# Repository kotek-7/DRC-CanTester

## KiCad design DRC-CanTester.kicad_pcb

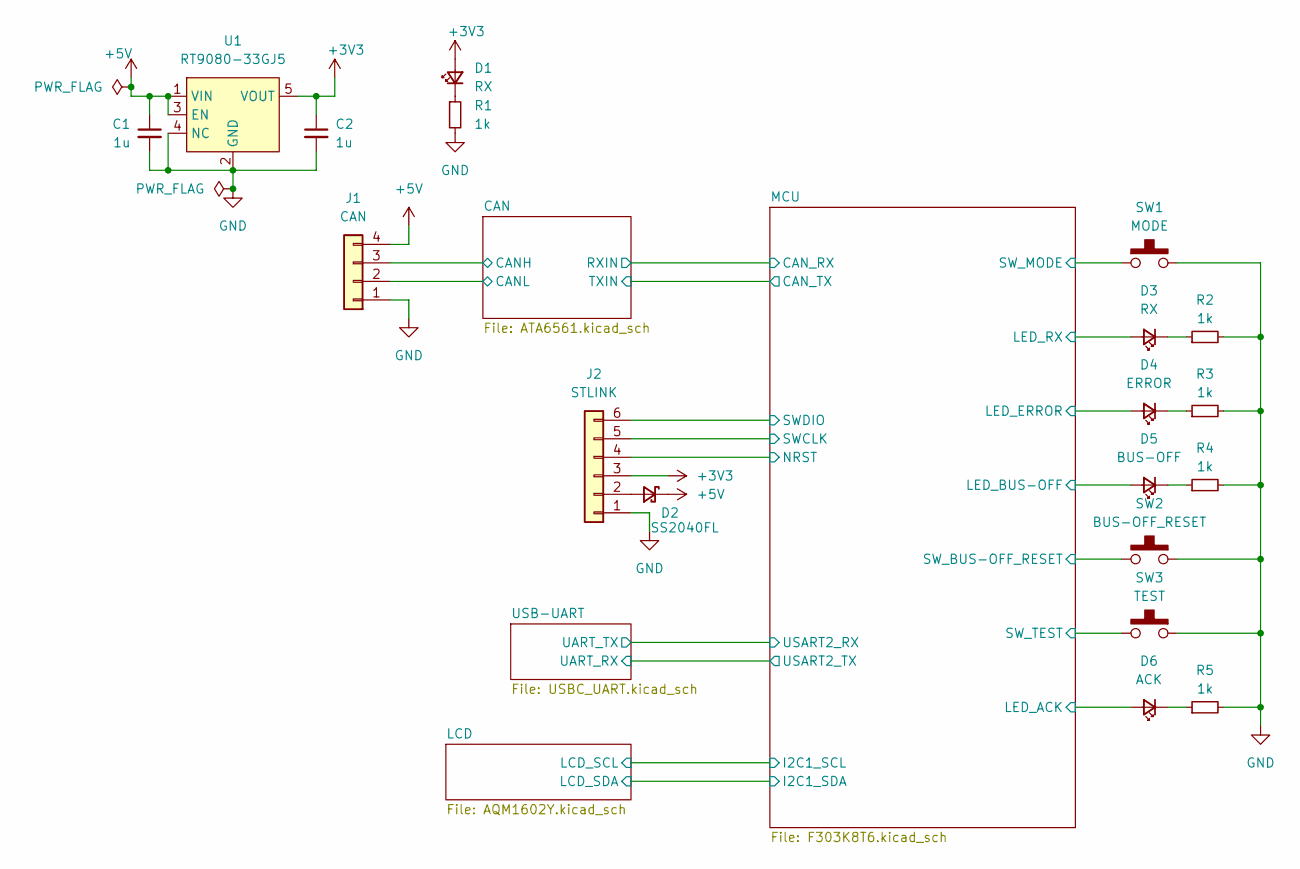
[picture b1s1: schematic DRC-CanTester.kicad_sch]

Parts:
C1, C2: 1u; C_0805_2012Metric_Pad1.18x1.45mm_HandSolder
D1, D3: RX; LED_0603_1608Metric_Pad1.05x0.95mm_HandSolder
D2: SS2040FL; D_SOD-123F
D4: ERROR; LED_0603_1608Metric_Pad1.05x0.95mm_HandSolder
D5: BUS-OFF; LED_0603_1608Metric_Pad1.05x0.95mm_HandSolder
D6: ACK; LED_0603_1608Metric_Pad1.05x0.95mm_HandSolder
J1: CAN; JST_XH_S4B-XH-A_1x04_P2.50mm_Horizontal; LCSC x
J2: STLINK; IDC-Header_2x03_P2.54mm_Vertical
R1, R2, R3, R4, R5: 1k; R_0603_1608Metric_Pad0.98x0.95mm_HandSolder
SW1: MODE; TS-06104
SW2: BUS-OFF_RESET; TS-06104
SW3: TEST; TS-06104
U1: RT9080-33GJ5; TSOT-23-5

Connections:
+3V3: C2.1, D1.2 (A), J2.3, U1.5 (VOUT); also elsewhere on the board
+5V: C1.1, D2.1 (K), J1.4, U1.1 (VIN), U1.3 (EN); also elsewhere on the board
/CAN/CANH: J1.3; also elsewhere on the board
/CAN/CANL: J1.2; also elsewhere on the board
/MCU/LED_ACK: D6.2 (A); also elsewhere on the board
/MCU/LED_BUS-OFF: D5.2 (A); also elsewhere on the board
/MCU/LED_ERROR: D4.2 (A); also elsewhere on the board
/MCU/LED_RX: D3.2 (A); also elsewhere on the board
/MCU/NRST: J2.4; also elsewhere on the board
/MCU/SWCLK: J2.5; also elsewhere on the board
/MCU/SWDIO: J2.6; also elsewhere on the board
/MCU/SW_BUS-OFF_RESET: SW2.3 (C), SW2.4 (D); also elsewhere on the board
/MCU/SW_MODE: SW1.1 (A), SW1.2 (B); also elsewhere on the board
/MCU/SW_TEST: SW3.3 (C), SW3.4 (D); also elsewhere on the board
GND: C1.2, C2.2, J1.1, J2.1, R1.2, R2.2, R3.2, R4.2, R5.2, SW1.3 (C), SW1.4 (D), SW2.1 (A), SW2.2 (B), SW3.1 (A), SW3.2 (B), U1.2 (GND), U1.4 (NC); also elsewhere on the board
unnamed 23: D1.1 (K), R1.1; also elsewhere on the board
unnamed: D2.2 (A), J2.2
unnamed: D3.1 (K), R2.1
unnamed: D4.1 (K), R3.1
unnamed: D5.1 (K), R4.1
unnamed: D6.1 (K), R5.1

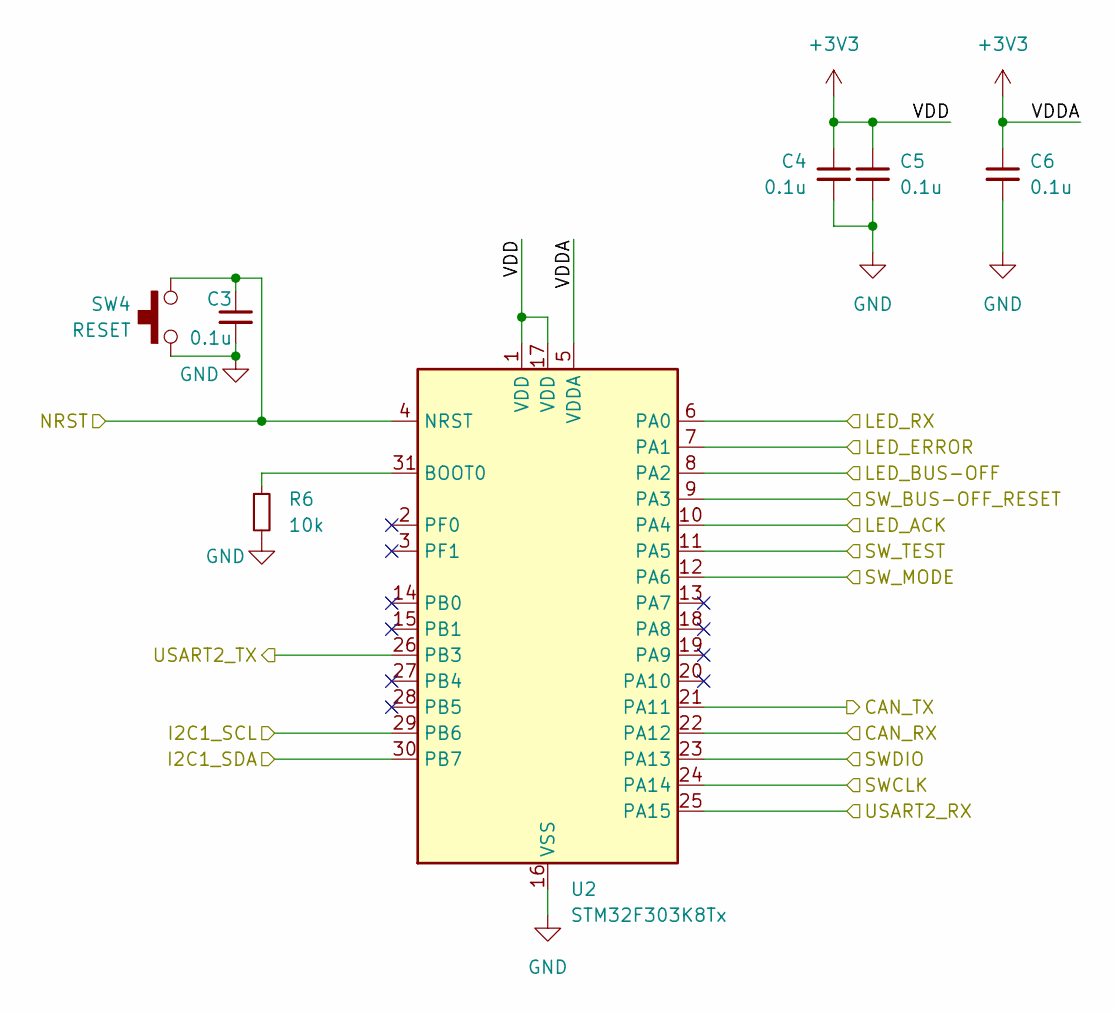
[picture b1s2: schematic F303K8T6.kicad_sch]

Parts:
C3, C4, C5, C6: 0.1u; C_0603_1608Metric_Pad1.08x0.95mm_HandSolder
R6: 10k; R_0603_1608Metric_Pad0.98x0.95mm_HandSolder
SW4: RESET; TVAF06-A020B-R
U2: STM32F303K8Tx; LQFP-32_7x7mm_P0.8mm

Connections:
+3V3: C4.1, C5.1, C6.1, U2.1 (VDD), U2.5 (VDDA), U2.17 (VDD); also elsewhere on the board
/CAN/RXIN: U2.22 (PA12); also elsewhere on the board
/CAN/TXIN: U2.21 (PA11); also elsewhere on the board
/LCD/LCD_SCL: U2.29 (PB6); also elsewhere on the board
/LCD/LCD_SDA: U2.30 (PB7); also elsewhere on the board
/MCU/LED_ACK: U2.10 (PA4); also elsewhere on the board
/MCU/LED_BUS-OFF: U2.8 (PA2); also elsewhere on the board
/MCU/LED_ERROR: U2.7 (PA1); also elsewhere on the board
/MCU/LED_RX: U2.6 (PA0); also elsewhere on the board
/MCU/NRST: C3.1, SW4.2, U2.4 (NRST); also elsewhere on the board
/MCU/SWCLK: U2.24 (PA14); also elsewhere on the board
/MCU/SWDIO: U2.23 (PA13); also elsewhere on the board
/MCU/SW_BUS-OFF_RESET: U2.9 (PA3); also elsewhere on the board
/MCU/SW_MODE: U2.12 (PA6); also elsewhere on the board
/MCU/SW_TEST: U2.11 (PA5); also elsewhere on the board
/MCU/USART2_RX: U2.25 (PA15); also elsewhere on the board
/MCU/USART2_TX: U2.26 (PB3); also elsewhere on the board
GND: C3.2, C4.2, C5.2, C6.2, R6.2, SW4.1 (2), U2.16 (VSS), U2.32 (VSS); also elsewhere on the board
unnamed: R6.1, U2.31 (BOOT0)

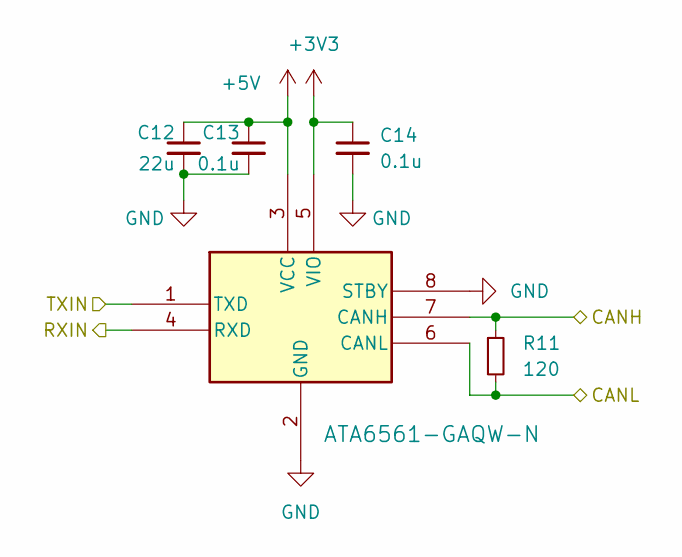
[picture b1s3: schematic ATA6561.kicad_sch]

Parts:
C12: 22u; C_0805_2012Metric_Pad1.18x1.45mm_HandSolder
C13, C14: 0.1u; C_0603_1608Metric_Pad1.08x0.95mm_HandSolder
R11: 120; R_0603_1608Metric_Pad0.98x0.95mm_HandSolder
U4: ATA6561-GAQW-N; SOIC8_4P9X3P9MC_MCH

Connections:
+3V3: C14.1, U4.5 (VIO); also elsewhere on the board
+5V: C12.1, C13.1, U4.3 (VCC); also elsewhere on the board
/CAN/CANH: R11.1, U4.7 (CANH); also elsewhere on the board
/CAN/CANL: R11.2, U4.6 (CANL); also elsewhere on the board
/CAN/RXIN: U4.4 (RXD); also elsewhere on the board
/CAN/TXIN: U4.1 (TXD); also elsewhere on the board
GND: C12.2, C13.2, C14.2, U4.2 (GND), U4.8 (STBY); also elsewhere on the board

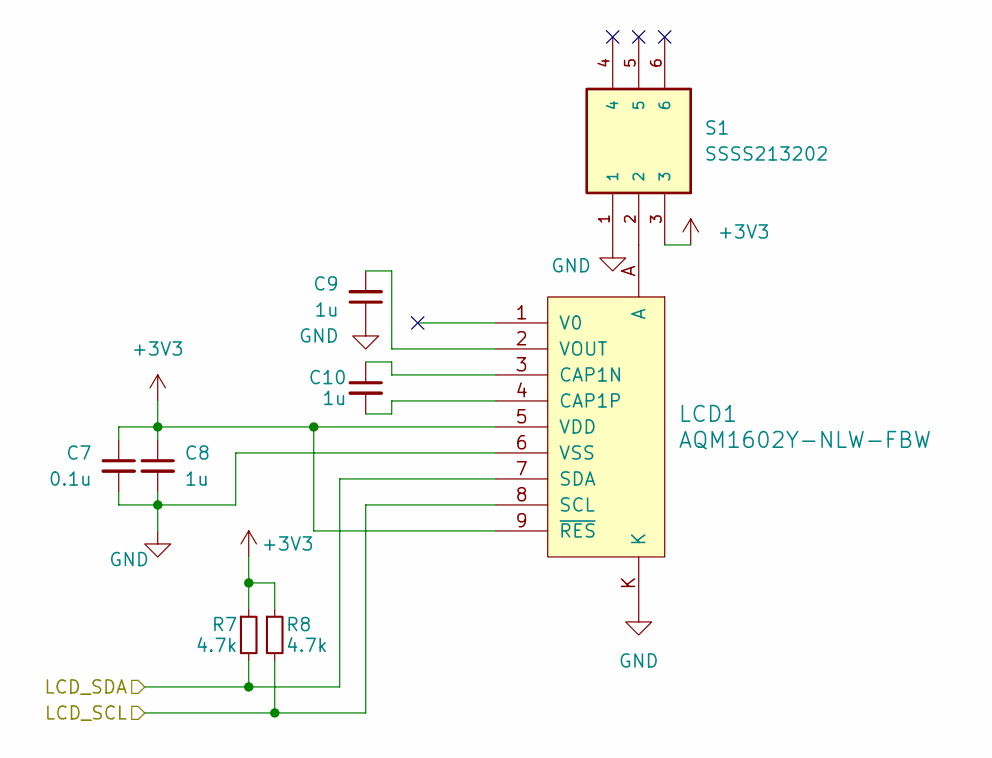
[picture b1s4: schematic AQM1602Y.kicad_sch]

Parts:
C7: 0.1u; C_0603_1608Metric_Pad1.08x0.95mm_HandSolder
C8, C9, C10: 1u; C_0603_1608Metric_Pad1.08x0.95mm_HandSolder
LCD1: AQM1602Y-NLW-FBW; AQM1602Y-NLW
R7, R8: 4.7k; R_0603_1608Metric_Pad0.98x0.95mm_HandSolder
S1: SSSS213202; MANUFACTURER_PART_NUMBER SSSS213202

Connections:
+3V3: C7.1, C8.1, LCD1.5 (VDD), LCD1.9 (~RES), R7.1, R8.1, S1.3; also elsewhere on the board
/LCD/LCD_SCL: LCD1.8 (SCL), R8.2; also elsewhere on the board
/LCD/LCD_SDA: LCD1.7 (SDA), R7.2; also elsewhere on the board
GND: C7.2, C8.2, C9.1, LCD1.6 (VSS), LCD1.K, S1.1; also elsewhere on the board
unnamed: C10.1, LCD1.3 (CAP1N)
unnamed: C10.2, LCD1.4 (CAP1P)
unnamed: LCD1.A, S1.2
unnamed: C9.2, LCD1.2 (VOUT)

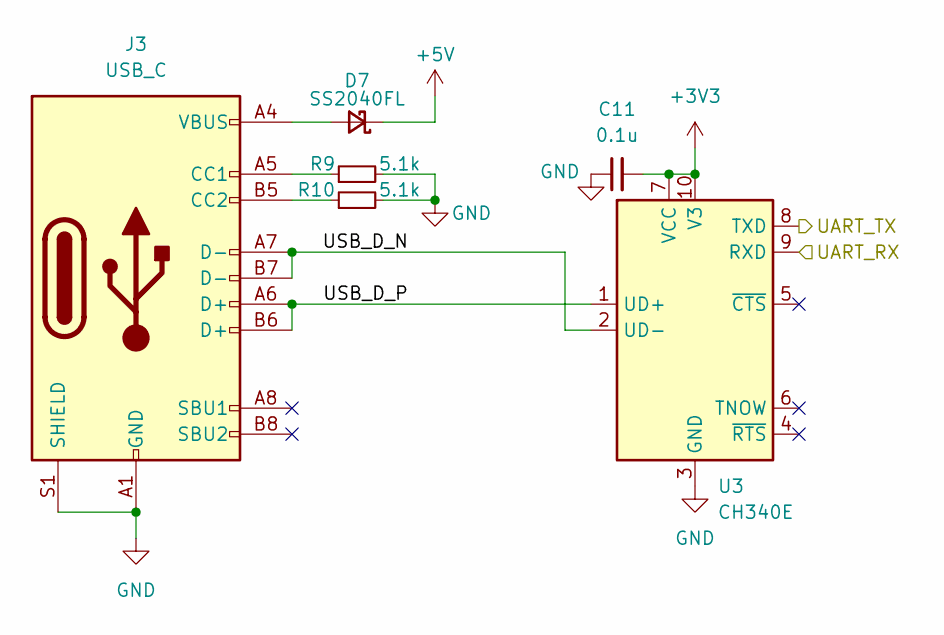
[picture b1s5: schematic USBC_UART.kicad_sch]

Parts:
C11: 0.1u; C_0603_1608Metric_Pad1.08x0.95mm_HandSolder
D7: SS2040FL; D_SOD-123F
J3: USB_C; USB_C_Receptacle_GCT_USB4105-xx-A_16P_TopMnt_Horizontal
R9, R10: 5.1k; R_0603_1608Metric_Pad0.98x0.95mm_HandSolder
U3: CH340E; MSOP-10_3x3mm_P0.5mm

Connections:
+3V3: C11.2, U3.7 (VCC), U3.10 (V3); also elsewhere on the board
+5V: D7.1 (K); also elsewhere on the board
/MCU/USART2_RX: U3.8 (TXD); also elsewhere on the board
/MCU/USART2_TX: U3.9 (RXD); also elsewhere on the board
/USB-UART/USB_D_N: J3.A7 (D-), J3.B7 (D-), U3.2 (UD-)
/USB-UART/USB_D_P: J3.A6 (D+), J3.B6 (D+), U3.1 (UD+)
GND: C11.1, J3.A1 (GND), J3.A12 (GND), J3.B1 (GND), J3.B12 (GND), J3.S1 (SHIELD), R9.2, R10.2, U3.3 (GND); also elsewhere on the board
unnamed: D7.2 (A), J3.A4 (VBUS), J3.A9 (VBUS), J3.B4 (VBUS), J3.B9 (VBUS)
unnamed: J3.A5 (CC1), R9.1
unnamed: J3.B5 (CC2), R10.1

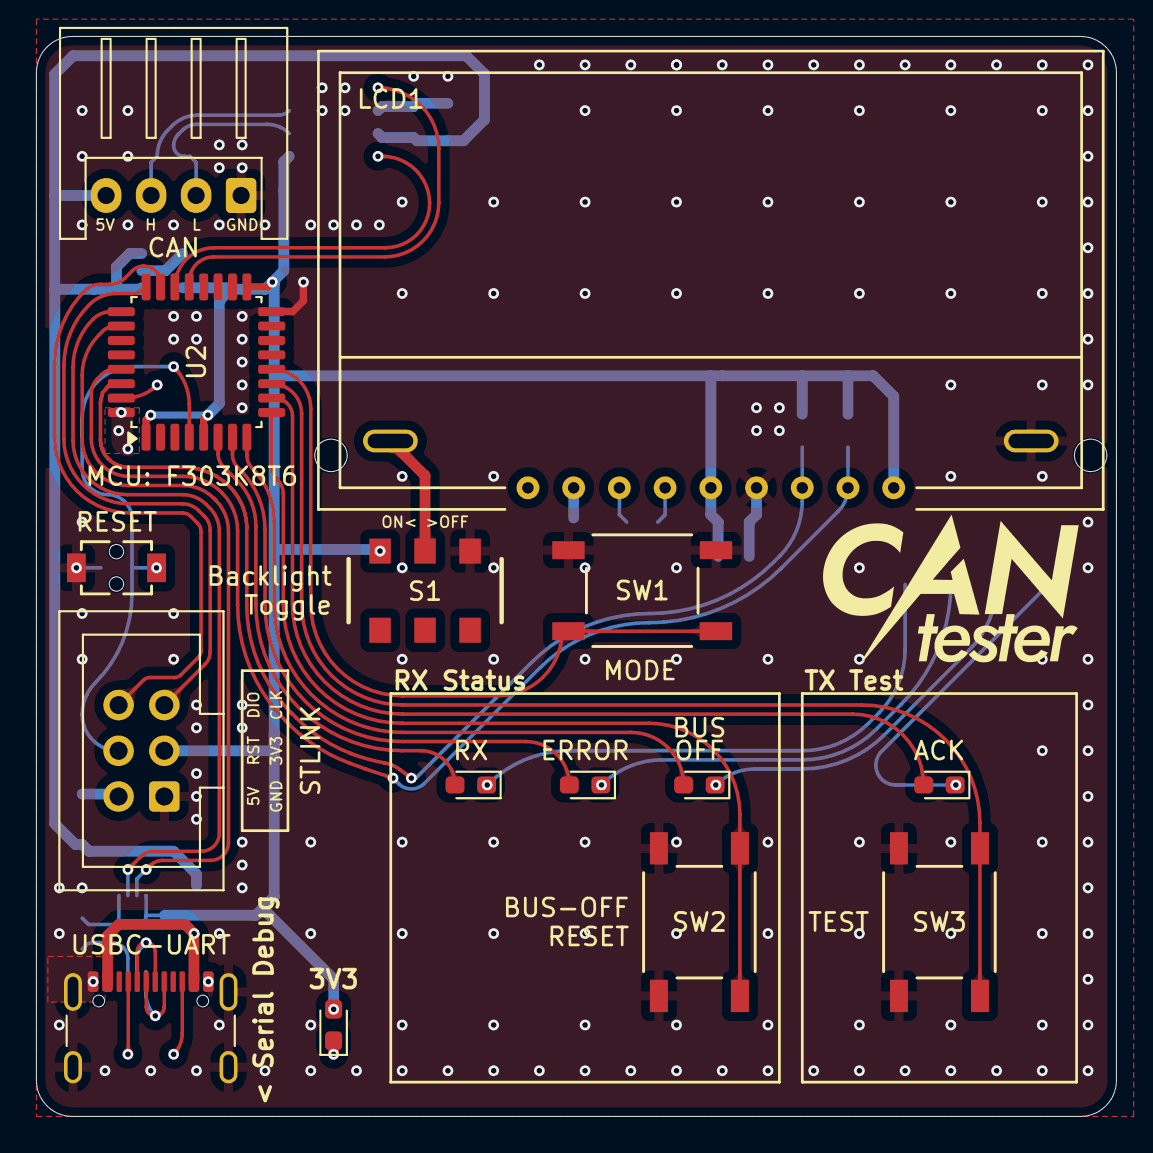
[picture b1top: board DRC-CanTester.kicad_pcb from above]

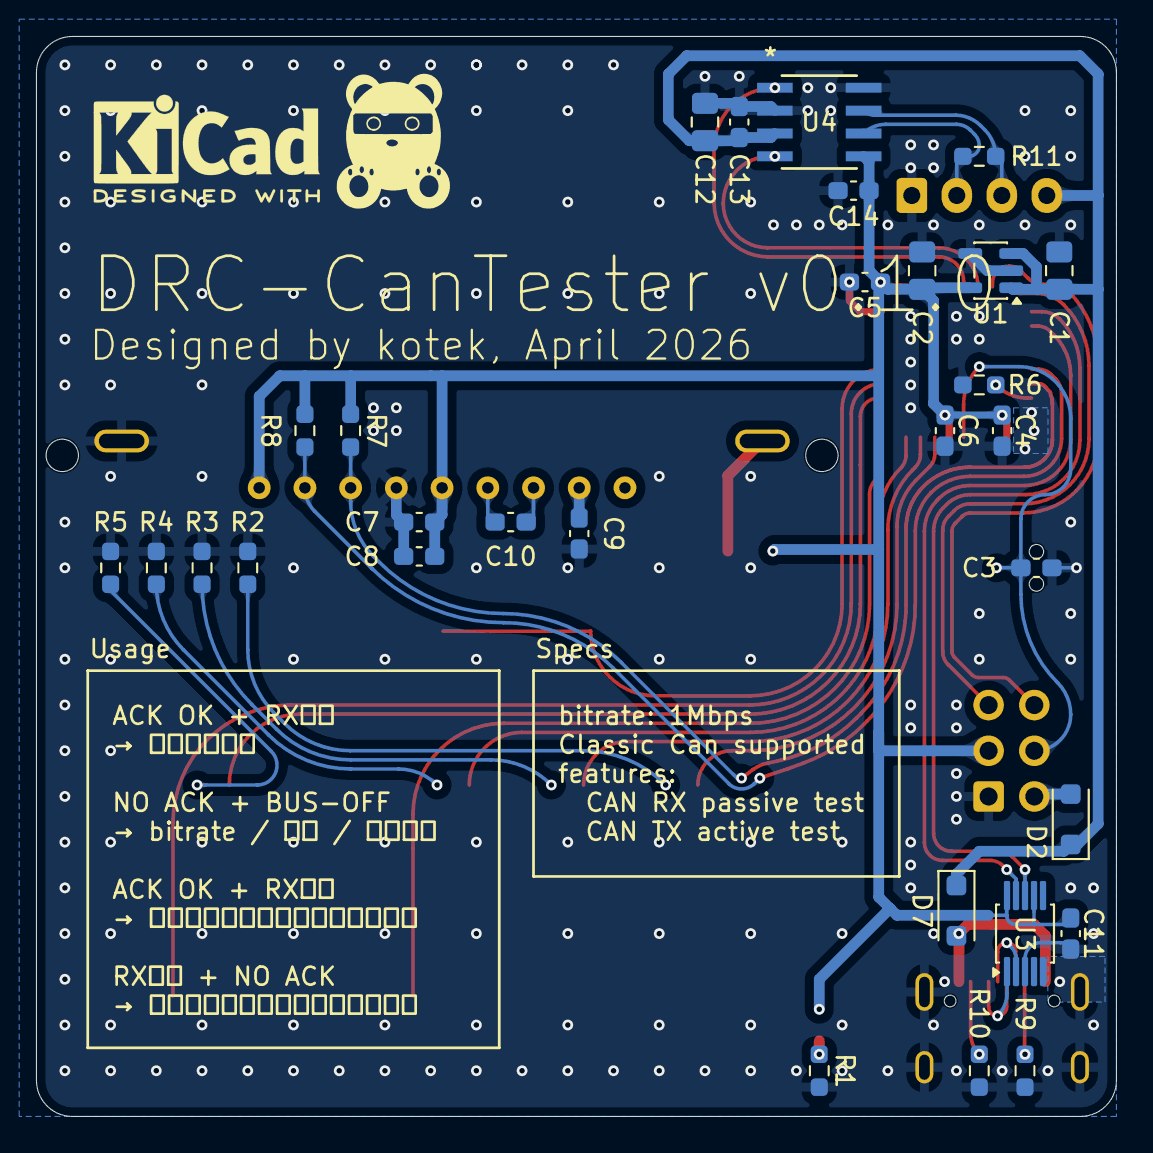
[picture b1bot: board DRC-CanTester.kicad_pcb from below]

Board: 2 copper layers, 60.0 x 60.0 mm, 45 parts (30 on the bottom side), 37 nets.

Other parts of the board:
3V3: RX; LED_0603_1608Metric_Pad1.05x0.95mm_HandSolder

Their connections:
+3V3: 3V3.2 (A); also elsewhere on the board
unnamed 23: 3V3.1 (K); also elsewhere on the board

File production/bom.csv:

Designator,Footprint,Quantity,Value,LCSC Part #
"3V3, D3",0603,2,RX,
"C1, C2",0805,2,1u,
"C10, C8, C9",0603,3,1u,
"C11, C13, C14, C3, C4, C5, C6, C7",0603,8,0.1u,
C12,0805,1,22u,
"D2, D7",D_SOD-123F,2,SS2040FL,
D4,0603,1,ERROR,
D5,0603,1,BUS-OFF,
D6,0603,1,ACK,
J1,JST_XH_S4B-XH-A_1x04_P2.50mm_Horizontal,1,CAN,x
J2,IDC-Header_2x03_P2.54mm_Vertical,1,STLINK,
J3,USB_C_Receptacle_GCT_USB4105-xx-A_16P_TopMnt_Horizontal,1,USB_C,
LCD1,AQM1602Y-NLW,1,AQM1602Y-NLW-FBW,
"R1, R2, R3, R4, R5",0603,5,1k,
"R10, R9",0603,2,5.1k,
R11,0603,1,120,
R6,0603,1,10k,
"R7, R8",0603,2,4.7k,
S1,SSSS213202,1,SSSS213202,
SW1,TS-06104,1,MODE,
SW2,TS-06104,1,BUS-OFF_RESET,
SW3,TS-06104,1,TEST,
SW4,TVAF06-A020B-R,1,RESET,
U1,TSOT-23-5,1,RT9080-33GJ5,
U2,LQFP-32_7x7mm_P0.8mm,1,STM32F303K8Tx,
U3,MSOP-10_3x3mm_P0.5mm,1,CH340E,
U4,SOIC8_4P9X3P9MC_MCH,1,ATA6561-GAQW-N,

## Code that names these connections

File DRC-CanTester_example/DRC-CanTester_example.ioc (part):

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Mcu.Name=STM32F303K(6-8)Tx
Mcu.Package=LQFP32
Mcu.UserName=STM32F303K8Tx
PA0.GPIOParameters=GPIO_Label
PA0.GPIO_Label=LED_RX
PA0.Signal=GPIO_Output
PA1.GPIOParameters=GPIO_Label
PA1.GPIO_Label=LED_ERROR
PA1.Signal=GPIO_Output
PA11.Mode=CAN_Activate
PA11.Signal=CAN_RX
PA12.Mode=CAN_Activate
PA12.Signal=CAN_TX
PA13.Mode=Serial_Wire
PA13.Signal=SYS_JTMS-SWDIO
PA14.Mode=Serial_Wire
PA14.Signal=SYS_JTCK-SWCLK
PA15.Mode=Asynchronous
PA15.Signal=USART2_RX
PA2.GPIOParameters=GPIO_Label
PA2.GPIO_Label=LED_BUS-OFF
PA2.Signal=GPIO_Output
PA3.GPIOParameters=GPIO_Label
PA3.GPIO_Label=SW_BUS-OFF_RESET
PA3.Signal=GPIO_Input
PA4.GPIOParameters=GPIO_Label
PA4.GPIO_Label=LED_ACK
PA4.Signal=GPIO_Output
PA5.GPIOParameters=GPIO_Label
PA5.GPIO_Label=SW_TEST
PA5.Signal=GPXTI5
PA6.GPIOParameters=GPIO_Label
PA6.GPIO_Label=SW_MODE
PA6.Signal=GPIO_Input
PB3.Mode=Asynchronous
PB3.Signal=USART2_TX
PB6.Mode=I2C
PB6.Signal=I2C1_SCL
PB7.Mode=I2C
PB7.Signal=I2C1_SDA
RCC.HSEPLLFreq_Value=8000000
RCC.HSE_VALUE=8000000
RCC.SYSCLKFreq_VALUE=60000000
RCC.SYSCLKSourceVirtual=RCC_SYSCLKSOURCE_PLLCLK
board=custom

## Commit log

2026-05-02 init, v0.1.0
2026-05-02 fabrication
2026-05-02 シルクを修正
2026-05-03 ガーバーファイルを再生成
